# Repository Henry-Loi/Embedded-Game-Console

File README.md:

### This project is inspired by Switch.

## Supported Games
- [X] Tetris
- [X] Asteroid
- [X] Pong
- [X] TicTacToe

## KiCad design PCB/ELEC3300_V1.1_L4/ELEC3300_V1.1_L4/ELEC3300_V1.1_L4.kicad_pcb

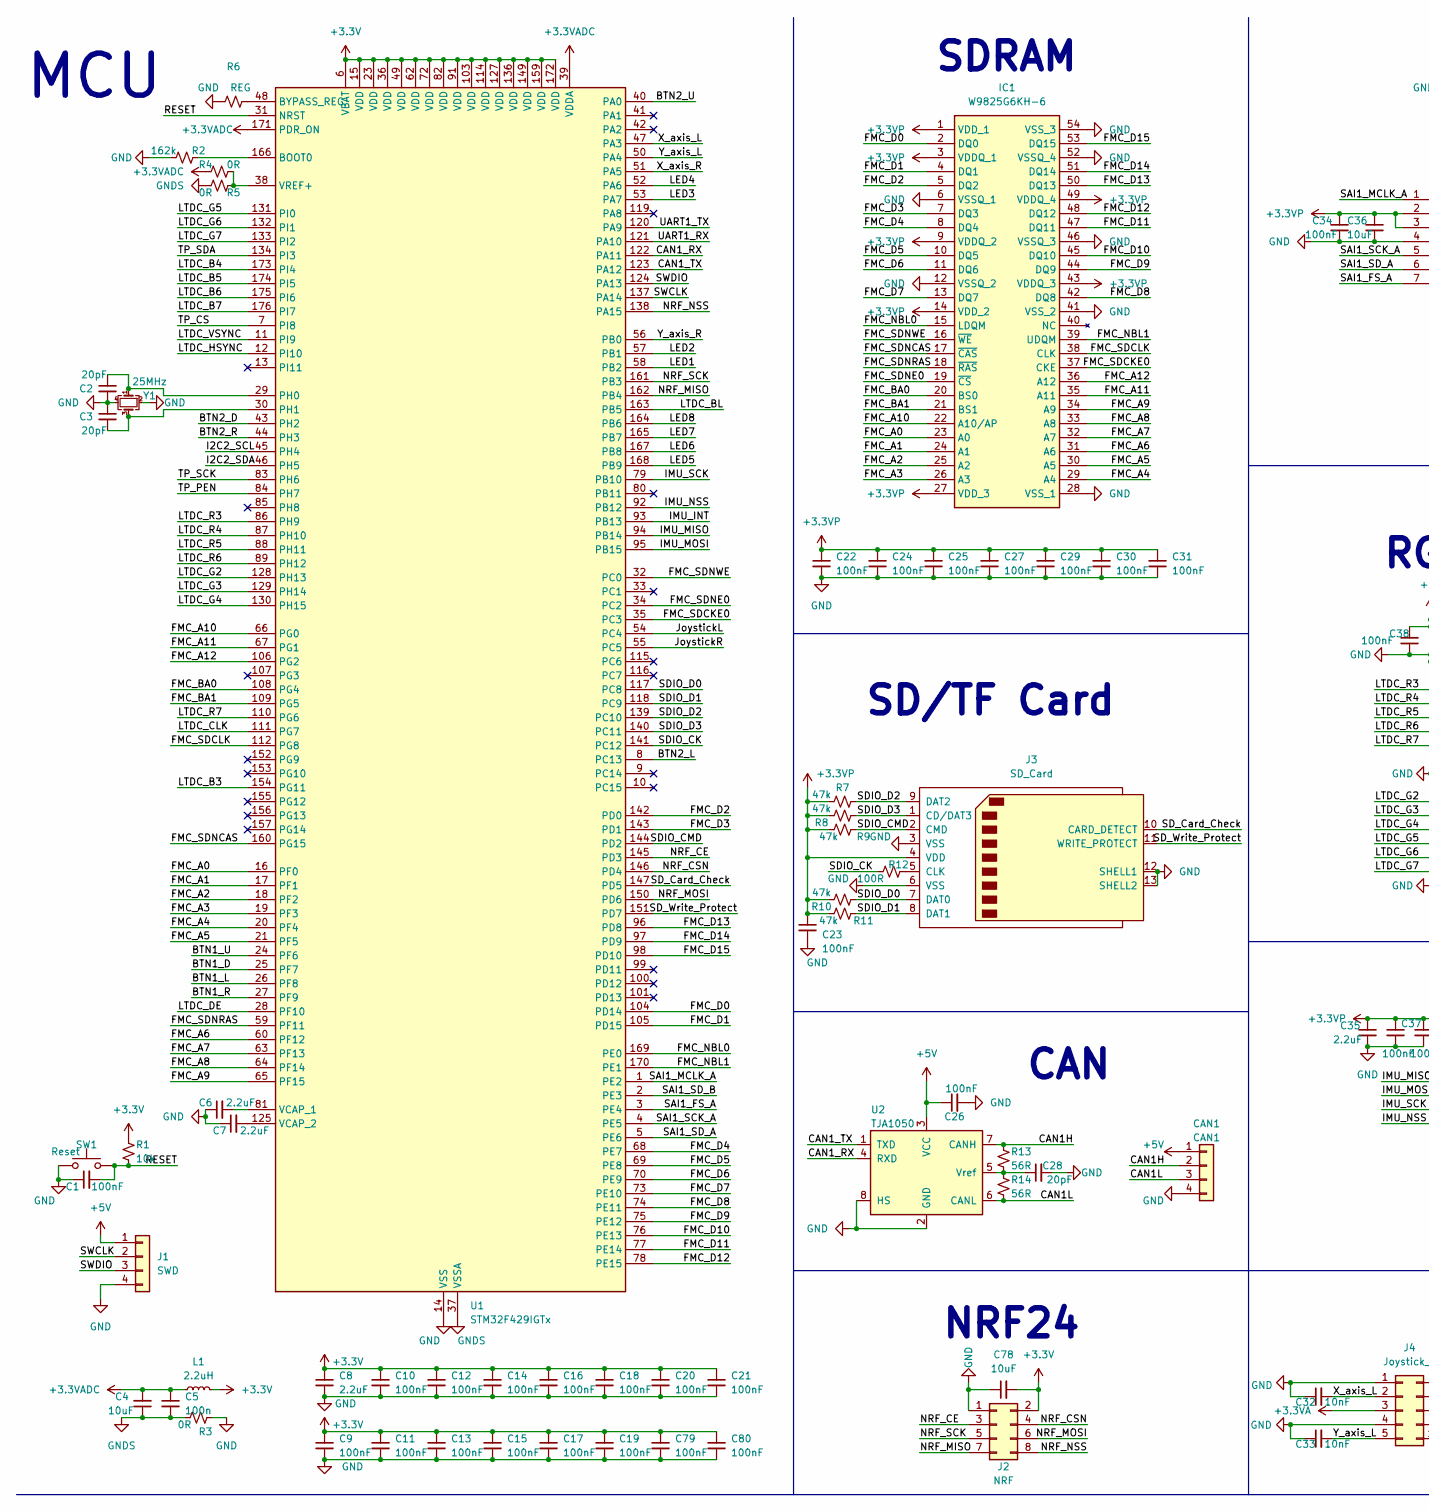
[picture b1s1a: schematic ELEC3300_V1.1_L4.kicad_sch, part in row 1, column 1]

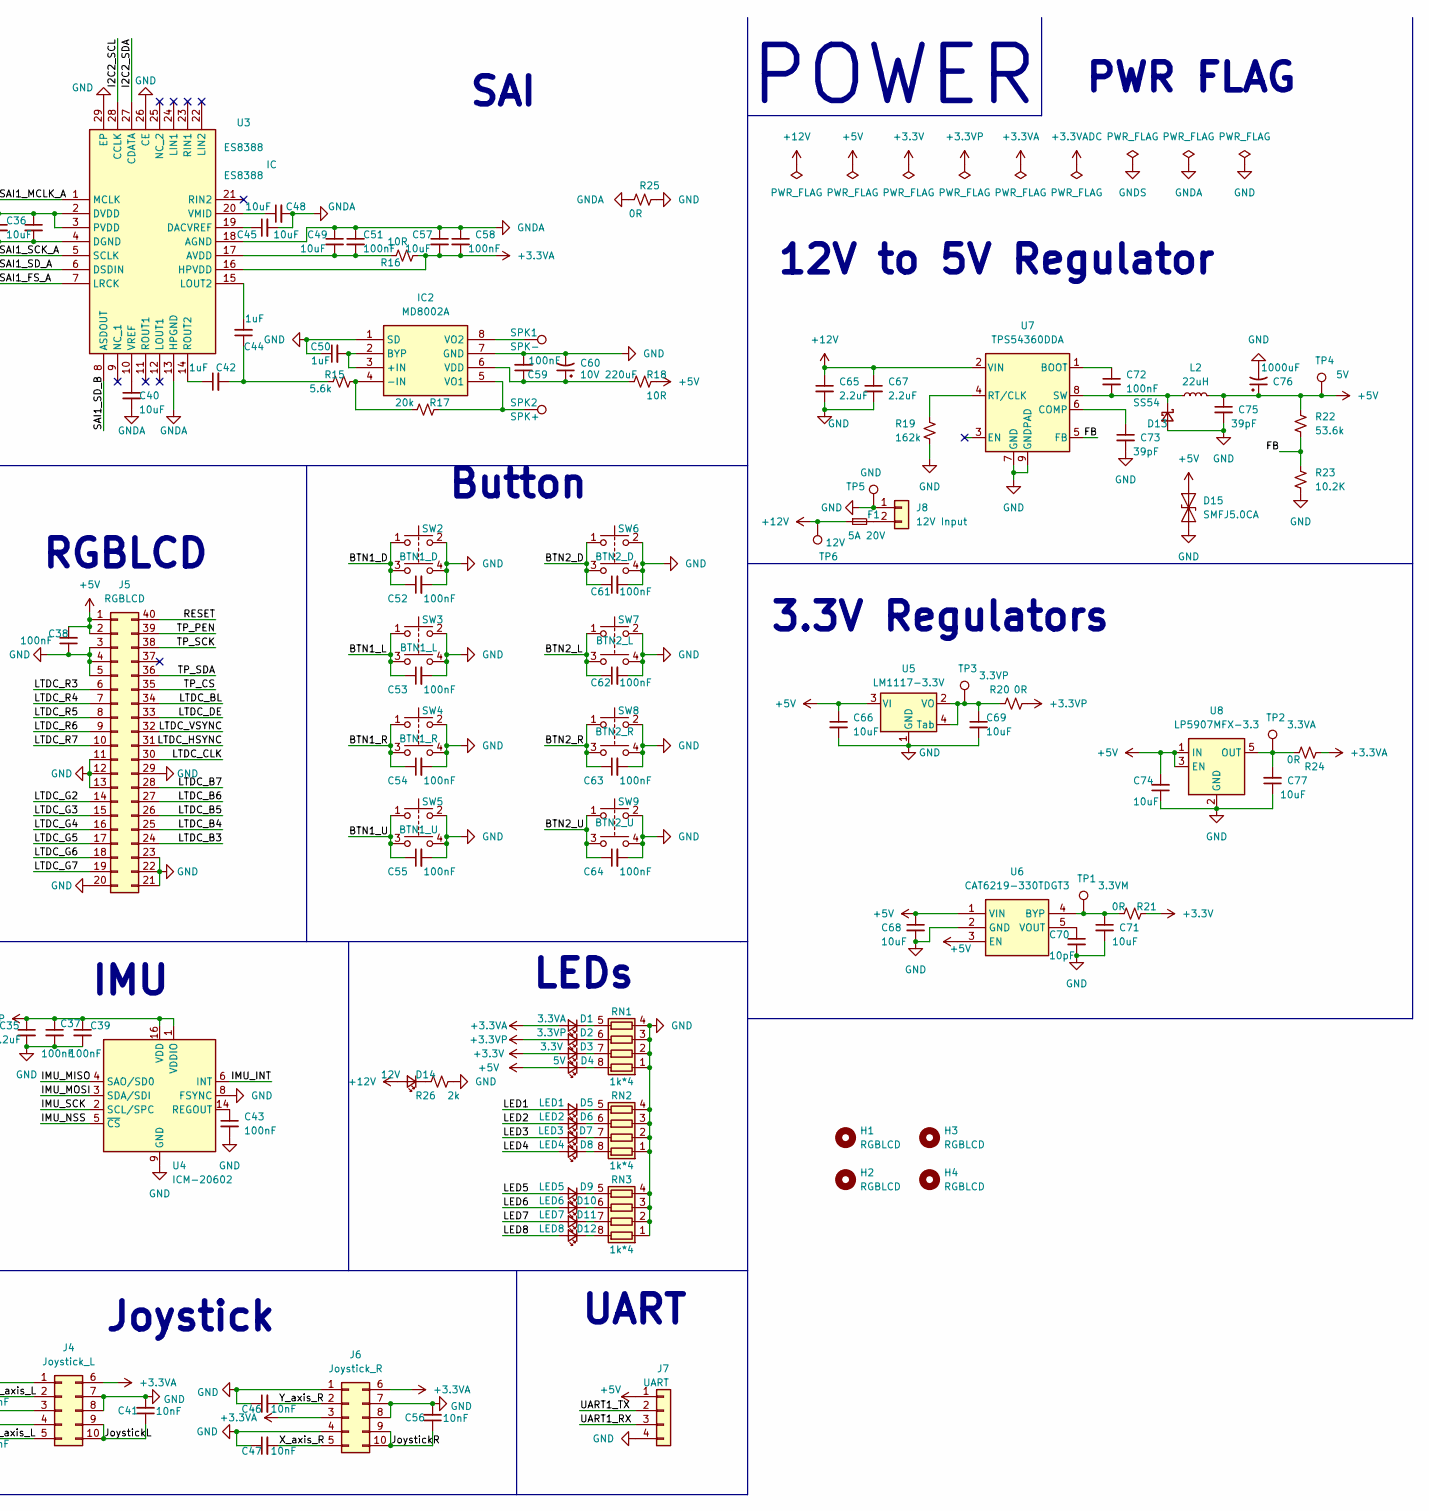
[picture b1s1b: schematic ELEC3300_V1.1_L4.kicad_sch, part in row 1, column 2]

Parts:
C1, C9, C10, C11, C12, C13, C14, C15, C16, C17, C18, C19, C20, C21, C22, C23, C24, C25, C26, C27, C29, C30, C31, C34, C37, C38, C39, C43, C51, C52, C53, C54, C55, C58, C61, C62, C63, C64, C72, C79, C80: 100nF; C_0402_1005Metric_Pad0.74x0.62mm_HandSolder
C2, C3, C28: 20pF; C_0402_1005Metric_Pad0.74x0.62mm_HandSolder
C4, C36, C45, C49, C57: 10uF; C_0402_1005Metric_Pad0.74x0.62mm_HandSolder
C5: 100n; C_0402_1005Metric_Pad0.74x0.62mm_HandSolder
C6, C7, C8, C35: 2.2uF; C_0402_1005Metric_Pad0.74x0.62mm_HandSolder
C32, C33, C41, C46, C47, C56: 10nF; C_0603_1608Metric
C40, C66, C68, C69, C71, C74, C77, C78: 10uF; C_0603_1608Metric
C42, C44, C50: 1uF; C_0603_1608Metric
C48: 10uF; R_0402_1005Metric_Pad0.72x0.64mm_HandSolder
C59: 100nF; C_0603_1608Metric
C60: 10V 220uF; CP_Elec_6.3x5.4
C65, C67: 2.2uF; C_0603_1608Metric
C70: 10pF; C_0603_1608Metric
C73, C75: 39pF; C_0603_1608Metric
C76: 1000uF; CP_Elec_8x10.5
CAN1: CAN1; Molex_SL_171971-0004_1x04_P2.54mm_Vertical
D1: 3.3VA; LED_0603_1608Metric
D2: 3.3VP; LED_0603_1608Metric
D3: 3.3V; LED_0603_1608Metric
D4: 5V; LED_0603_1608Metric
D5: LED1; LED_0603_1608Metric
D6: LED2; LED_0603_1608Metric
D7: LED3; LED_0603_1608Metric
D8: LED4; LED_0603_1608Metric
D9: LED5; LED_0603_1608Metric
D10: LED6; LED_0603_1608Metric
D11: LED7; LED_0603_1608Metric
D12: LED8; LED_0603_1608Metric
D13: SS54; D_SMA
D14: 12V; LED_0603_1608Metric
D15: SMFJ5.0CA; D_SOD-123F
F1: 5A 20V; 1808Fuse_Base
H1, H2, H3, H4: RGBLCD; MountingHole_3.2mm_M3
IC1: W9825G6KH-6; SOP80P1176X120-54N; Manufacturer_Part_Number W9825G6KH-6; Mouser Part Number 454-W9825G6KH-6
IC2: MD8002A; SOIC127P600X175-8N; Manufacturer_Part_Number MD8002A
J1: SWD; Molex_SL_171971-0004_1x04_P2.54mm_Vertical
J2: NRF; PinHeader_2x04_P2.54mm_Vertical
J3: SD_Card; SD_Kyocera_145638009511859+
J4: Joystick_L; XDCR_COM-09032
J5: RGBLCD; Hirose_FH12-40S-0.5SH_1x40-1MP_P0.50mm_Horizontal
J6: Joystick_R; XDCR_COM-09032
J7: UART; Molex_SL_171971-0004_1x04_P2.54mm_Vertical
J8: 12V Input; AMASS_XT30U-M_1x02_P5.0mm_Vertical
L1: 2.2uH; L_0420
L2: 22uH; L_7.3x7.3_H3.5
R1: 10k; R_0402_1005Metric_Pad0.72x0.64mm_HandSolder
R2: 162k; L_0402_1005Metric_Pad0.77x0.64mm_HandSolder
R3, R4, R5, R25: 0R; R_0402_1005Metric_Pad0.72x0.64mm_HandSolder
R6: REG; R_0402_1005Metric_Pad0.72x0.64mm_HandSolder
R7, R8, R9, R10, R11: 47k; R_0402_1005Metric_Pad0.72x0.64mm_HandSolder
R12: 100R; R_0402_1005Metric_Pad0.72x0.64mm_HandSolder
R13, R14: 56R; R_0402_1005Metric_Pad0.72x0.64mm_HandSolder
R15: 5.6k; R_0603_1608Metric
R16, R18: 10R; R_0603_1608Metric
R17: 20k; R_0603_1608Metric
R19: 162k; R_0603_1608Metric
R20, R21, R24: 0R; R_0603_1608Metric_Pad0.98x0.95mm_HandSolder
R22: 53.6k; R_0402_1005Metric_Pad0.72x0.64mm_HandSolder
R23: 10.2K; R_0402_1005Metric_Pad0.72x0.64mm_HandSolder
R26: 2k; R_0603_1608Metric_Pad0.98x0.95mm_HandSolder
RN1, RN2, RN3: 1k*4; R_Array_Concave_4x0402
SPK1: SPK-; TestPoint_Loop_D3.50mm_Drill1.4mm_Beaded
SPK2: SPK+; TestPoint_Loop_D3.50mm_Drill1.4mm_Beaded
SW1: Reset; SW_Push_1P1T_NO_CK_KSC6xxJ
SW2: BTN1_D; SW_B3F-4055
SW3: BTN1_L; SW_B3F-4055
SW4: BTN1_R; SW_B3F-4055
SW5: BTN1_U; SW_B3F-4055
SW6: BTN2_D; SW_B3F-4055
SW7: BTN2_L; SW_B3F-4055
SW8: BTN2_R; SW_B3F-4055
SW9: BTN2_U; SW_B3F-4055
TP1: 3.3VM; TestPoint_Pad_D2.5mm
TP2: 3.3VA; TestPoint_Pad_D2.5mm
TP3: 3.3VP; TestPoint_Pad_D2.5mm
TP4: 5V; TestPoint_Pad_D2.5mm
TP5: GND; TestPoint_Pad_D2.5mm
TP6: 12V; TestPoint_Pad_D2.5mm
U1: STM32F429IGTx; LQFP-176_24x24mm_P0.5mm
U2: TJA1050; SOIC-8_3.9x4.9mm_P1.27mm
U3: ES8388; QFN45P400X400X90-29N-D; Manufacturer_Part_Number ES8388
U4: ICM-20602; LGA-16_3x3mm_P0.5mm_LayoutBorder3x5y
U5: LM1117-3.3V; SOT-223
U6: CAT6219-330TDGT3; SOT95P280X100-5N; Manufacturer_Part_Number CAT6219-330TDGT3; Mouser Part Number 698-CAT6219-330TD-G
U7: TPS54360DDA; TI_SO-PowerPAD-8_ThermalVias
U8: LP5907MFX-3.3; SOT-23-5
Y1: 25MHz; Crystal_SMD_3225-4Pin_3.2x2.5mm

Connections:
+3.3V: C8.1, C9.1, C10.1, C11.1, C12.1, C13.1, C14.1, C15.1, C16.1, C17.1, C18.1, C19.1, C20.1, C21.1, C78.2, C79.1, C80.1, D3.2 (A), J2.2, L1.2, R1.2, R21.2, U1.6 (VBAT), U1.15 (VDD), U1.23 (VDD), U1.36 (VDD), U1.49 (VDD), U1.62 (VDD), U1.72 (VDD), U1.82 (VDD), U1.91 (VDD), U1.103 (VDD), U1.114 (VDD), U1.127 (VDD), U1.136 (VDD), U1.149 (VDD), U1.159 (VDD), U1.172 (VDD)
+3.3VA: C57.2, C58.2, D1.2 (A), J4.3, J4.6, J6.3, J6.6, R16.2, R24.2, U3.16 (HPVDD)
+3.3VADC: C4.2, C5.1, L1.1, R4.1, U1.39 (VDDA), U1.171 (PDR_ON)
+3.3VP: C22.1, C23.1, C24.1, C25.1, C27.1, C29.1, C30.1, C31.1, C34.1, C35.1, C36.1, C37.1, C39.1, D2.2 (A), IC1.1 (VDD_1), IC1.3 (VDDQ_1), IC1.9 (VDDQ_2), IC1.14 (VDD_2), IC1.27 (VDD_3), IC1.43 (VDDQ_3), IC1.49 (VDDQ_4), J3.4 (VDD), R7.1, R8.1, R9.1, R10.1, R11.1, R20.2, U3.2 (DVDD), U3.3 (PVDD), U4.1 (VDDIO), U4.16 (VDD)
+5V: C26.1, C38.2, C66.1, C68.1, C74.2, C75.1, C76.1, CAN1.1, D4.2 (A), D15.1 (A1), J1.1, J5.1, J5.2, J7.1, L2.2, R18.2, R22.1, TP4.1, U2.3 (VCC), U5.3 (VI), U6.1 (VIN), U6.3 (EN), U8.1 (IN), U8.3 (EN)
+12V: C65.1, C67.1, D14.2 (A), F1.1, TP6.1, U7.2 (VIN)
/BTN1_D: C52.1, SW2.1, SW2.3, U1.25 (PF7)
/BTN1_L: C53.1, SW3.1, SW3.3, U1.26 (PF8)
/BTN1_R: C54.1, SW4.1, SW4.3, U1.27 (PF9)
/BTN1_U: C55.1, SW5.1, SW5.3, U1.24 (PF6)
/BTN2_D: C61.1, SW6.1, SW6.3, U1.43 (PH2)
/BTN2_L: C62.1, SW7.1, SW7.3, U1.8 (PC13)
/BTN2_R: C63.1, SW8.1, SW8.3, U1.44 (PH3)
/BTN2_U: C64.1, SW9.1, SW9.3, U1.40 (PA0)
/CAN1H: CAN1.2, R13.1, U2.7 (CANH)
/CAN1L: CAN1.3, R14.2, U2.6 (CANL)
/CAN1_RX: U1.122 (PA11), U2.4 (RXD)
/CAN1_TX: U1.123 (PA12), U2.1 (TXD)
/FB: R22.2, R23.1, U7.5 (FB)
/FMC_A0: IC1.23 (A0), U1.16 (PF0)
/FMC_A1: IC1.24 (A1), U1.17 (PF1)
/FMC_A2: IC1.25 (A2), U1.18 (PF2)
/FMC_A3: IC1.26 (A3), U1.19 (PF3)
/FMC_A4: IC1.29 (A4), U1.20 (PF4)
/FMC_A5: IC1.30 (A5), U1.21 (PF5)
/FMC_A6: IC1.31 (A6), U1.60 (PF12)
/FMC_A7: IC1.32 (A7), U1.63 (PF13)
/FMC_A8: IC1.33 (A8), U1.64 (PF14)
/FMC_A9: IC1.34 (A9), U1.65 (PF15)
/FMC_A10: IC1.22 (A10/AP), U1.66 (PG0)
/FMC_A11: IC1.35 (A11), U1.67 (PG1)
/FMC_A12: IC1.36 (A12), U1.106 (PG2)
/FMC_BA0: IC1.20 (BS0), U1.108 (PG4)
/FMC_BA1: IC1.21 (BS1), U1.109 (PG5)
/FMC_D0: IC1.2 (DQ0), U1.104 (PD14)
/FMC_D1: IC1.4 (DQ1), U1.105 (PD15)
/FMC_D2: IC1.5 (DQ2), U1.142 (PD0)
/FMC_D3: IC1.7 (DQ3), U1.143 (PD1)
/FMC_D4: IC1.8 (DQ4), U1.68 (PE7)
/FMC_D5: IC1.10 (DQ5), U1.69 (PE8)
/FMC_D6: IC1.11 (DQ6), U1.70 (PE9)
/FMC_D7: IC1.13 (DQ7), U1.73 (PE10)
/FMC_D8: IC1.42 (DQ8), U1.74 (PE11)
/FMC_D9: IC1.44 (DQ9), U1.75 (PE12)
/FMC_D10: IC1.45 (DQ10), U1.76 (PE13)
/FMC_D11: IC1.47 (DQ11), U1.77 (PE14)
/FMC_D12: IC1.48 (DQ12), U1.78 (PE15)
/FMC_D13: IC1.50 (DQ13), U1.96 (PD8)
/FMC_D14: IC1.51 (DQ14), U1.97 (PD9)
/FMC_D15: IC1.53 (DQ15), U1.98 (PD10)
/FMC_NBL0: IC1.15 (LDQM), U1.169 (PE0)
/FMC_NBL1: IC1.39 (UDQM), U1.170 (PE1)
/FMC_SDCKE0: IC1.37 (CKE), U1.35 (PC3)
/FMC_SDCLK: IC1.38 (CLK), U1.112 (PG8)
/FMC_SDNCAS: IC1.17 (~CAS), U1.160 (PG15)
/FMC_SDNE0: IC1.19 (~CS), U1.34 (PC2)
/FMC_SDNRAS: IC1.18 (~RAS), U1.59 (PF11)
/FMC_SDNWE: IC1.16 (~WE), U1.32 (PC0)
/I2C2_SCL: U1.45 (PH4), U3.28 (CCLK)
/I2C2_SDA: U1.46 (PH5), U3.27 (CDATA)
/IMU_INT: U1.93 (PB13), U4.6 (INT)
/IMU_MISO: U1.94 (PB14), U4.4 (SAO/SD0)
/IMU_MOSI: U1.95 (PB15), U4.3 (SDA/SDI)
/IMU_NSS: U1.92 (PB12), U4.5 (~CS)
/IMU_SCK: U1.79 (PB10), U4.2 (SCL/SPC)
/JoystickL: C41.1, J4.9, J4.10, U1.54 (PC4)
/JoystickR: C56.1, J6.9, J6.10, U1.55 (PC5)
/LED1: D5.2 (A), U1.58 (PB2)
/LED2: D6.2 (A), U1.57 (PB1)
/LED3: D7.2 (A), U1.53 (PA7)
/LED4: D8.2 (A), U1.52 (PA6)
/LED5: D9.2 (A), U1.168 (PB9)
/LED6: D10.2 (A), U1.167 (PB8)
/LED7: D11.2 (A), U1.165 (PB7)
/LED8: D12.2 (A), U1.164 (PB6)
/LTDC_B3: J5.24, U1.154 (PG11)
/LTDC_B4: J5.25, U1.173 (PI4)
/LTDC_B5: J5.26, U1.174 (PI5)
/LTDC_B6: J5.27, U1.175 (PI6)
/LTDC_B7: J5.28, U1.176 (PI7)
/LTDC_BL: J5.34, U1.163 (PB5)
/LTDC_CLK: J5.30, U1.111 (PG7)
/LTDC_DE: J5.33, U1.28 (PF10)
/LTDC_G2: J5.14, U1.128 (PH13)
/LTDC_G3: J5.15, U1.129 (PH14)
/LTDC_G4: J5.16, U1.130 (PH15)
/LTDC_G5: J5.17, U1.131 (PI0)
/LTDC_G6: J5.18, U1.132 (PI1)
/LTDC_G7: J5.19, U1.133 (PI2)
/LTDC_HSYNC: J5.31, U1.12 (PI10)
/LTDC_R3: J5.6, U1.86 (PH9)
/LTDC_R4: J5.7, U1.87 (PH10)
/LTDC_R5: J5.8, U1.88 (PH11)
/LTDC_R6: J5.9, U1.89 (PH12)
/LTDC_R7: J5.10, U1.110 (PG6)
/LTDC_VSYNC: J5.32, U1.11 (PI9)
/NRF_CE: J2.3, U1.145 (PD3)
/NRF_CSN: J2.4, U1.146 (PD4)
/NRF_MISO: J2.7, U1.162 (PB4)
/NRF_MOSI: J2.6, U1.150 (PD6)
/NRF_NSS: J2.8, U1.138 (PA15)
/NRF_SCK: J2.5, U1.161 (PB3)
/RESET: C1.2, J5.40, R1.1, SW1.2, U1.31 (NRST)
/SAI1_FS_A: U1.3 (PE4), U3.7 (LRCK)
/SAI1_MCLK_A: U1.1 (PE2), U3.1 (MCLK)
/SAI1_SCK_A: U1.4 (PE5), U3.5 (SCLK)
/SAI1_SD_A: U1.5 (PE6), U3.6 (DSDIN)
/SAI1_SD_B: U1.2 (PE3), U3.8 (ASDOUT)
/SDIO_CK: R12.1, U1.141 (PC12)
/SDIO_CMD: J3.2 (CMD), R9.2, U1.144 (PD2)
/SDIO_D0: J3.7 (DAT0), R10.2, U1.117 (PC8)
/SDIO_D1: J3.8 (DAT1), R11.2, U1.118 (PC9)
/SDIO_D2: J3.9 (DAT2), R7.2, U1.139 (PC10)
/SDIO_D3: J3.1 (CD/DAT3), R8.2, U1.140 (PC11)
/SD_Card_Check: J3.10 (CARD_DETECT), U1.147 (PD5)
/SD_Write_Protect: J3.11 (WRITE_PROTECT), U1.151 (PD7)
/SWCLK: J1.2, U1.137 (PA14)
/SWDIO: J1.3, U1.124 (PA13)
/TP_CS: J5.35, U1.7 (PI8)
/TP_PEN: J5.39, U1.84 (PH7)
/TP_SCK: J5.38, U1.83 (PH6)
/TP_SDA: J5.36, U1.134 (PI3)
/UART1_RX: J7.3, U1.121 (PA10)
/UART1_TX: J7.2, U1.120 (PA9)
/X_axis_L: C32.2, J4.2, U1.47 (PA3)
/X_axis_R: C47.2, J6.5, U1.51 (PA5)
/Y_axis_L: C33.2, J4.5, U1.50 (PA4)
/Y_axis_R: C46.2, J6.2, U1.56 (PB0)
GND: C1.1, C2.2, C3.1, C6.1, C7.1, C8.2, C9.2, C10.2, C11.2, C12.2, C13.2, C14.2, C15.2, C16.2, C17.2, C18.2, C19.2, C20.2, C21.2, C22.2, C23.2, C24.2, C25.2, C26.2, C27.2, C28.2, C29.2, C30.2, C31.2, C32.1, C33.1, C34.2, C35.2, C36.2, C37.2, C38.1, C39.2, C41.2, C43.2, C46.1, C47.1, C50.1, C52.2, C53.2, C54.2, C55.2, C56.2, C59.2, C60.2, C61.2, C62.2, C63.2, C64.2, C65.2, C66.2, C67.2, C68.2, C69.2, C70.2, C71.2, C73.2, C74.1, C75.2, C76.2, C77.1, C78.1, C79.2, C80.2, CAN1.4, D13.2 (A), D15.2 (A2), IC1.6 (VSSQ_1), IC1.12 (VSSQ_2), IC1.28 (VSS_1), IC1.41 (VSS_2), IC1.46 (VSSQ_3), IC1.52 (VSSQ_4), IC1.54 (VSS_3), IC2.1 (SD), IC2.7 (GND)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
GNDA: C40.2, C45.2, C48.2, C49.1, C51.1, C57.1, C58.1, R25.1, U3.13 (HPGND), U3.18 (AGND)
GNDS: C4.1, C5.2, R3.1, R5.1, U1.37 (VSSA)
unnamed: C42.2, C44.1, R15.1
unnamed: D1.1 (K), RN1.5 (R4.2)
unnamed: D2.1 (K), RN1.6 (R3.2)
unnamed: D3.1 (K), RN1.7 (R2.2)
unnamed: D4.1 (K), RN1.8 (R1.2)
unnamed: D5.1 (K), RN2.5 (R4.2)
unnamed: D6.1 (K), RN2.6 (R3.2)
unnamed: D7.1 (K), RN2.7 (R2.2)
unnamed: D8.1 (K), RN2.8 (R1.2)
unnamed: D9.1 (K), RN3.5 (R4.2)
unnamed: D10.1 (K), RN3.6 (R3.2)
unnamed: D11.1 (K), RN3.7 (R2.2)
unnamed: D12.1 (K), RN3.8 (R1.2)
unnamed: C72.2, D13.1 (K), L2.1, U7.8 (SW)
unnamed: D14.1 (K), R26.1
unnamed: C50.2, IC2.2 (BYP), IC2.3 (+IN)
unnamed: IC2.4 (-IN), R15.2, R17.1
unnamed: C59.1, C60.1, IC2.6 (VDD), R18.1
unnamed: IC2.5 (VO1), R17.2, SPK2.1
unnamed: IC2.8 (VO2), SPK1.1
unnamed: J3.5 (CLK), R12.2
unnamed: F1.2, J8.2
unnamed: R2.2, U1.166 (BOOT0)
unnamed: R6.2, U1.48 (BYPASS_REG)
unnamed: C2.1, U1.29 (PH0), Y1.1
unnamed: C3.2, U1.30 (PH1), Y1.3
unnamed: C6.2, U1.81 (VCAP_1)
unnamed: C7.2, U1.125 (VCAP_2)
unnamed: R4.2, R5.2, U1.38 (VREF+)
unnamed: C28.1, R13.2, R14.1, U2.5 (Vref)
unnamed: C49.2, C51.2, R16.1, U3.17 (AVDD)
unnamed: C45.1, U3.19 (DACVREF)
unnamed: C44.2, U3.15 (LOUT2)
unnamed: C42.1, U3.14 (ROUT2)
unnamed: C48.1, U3.20 (VMID)
unnamed: C40.1, U3.10 (VREF)
unnamed: C43.1, U4.14 (REGOUT)
unnamed: C69.1, R20.1, TP3.1, U5.2 (VO), U5.4 (Tab)
unnamed: C71.1, R21.1, TP1.1, U6.4 (BYP)
unnamed: C70.1, U6.5 (VOUT)
unnamed: C72.1, U7.1 (BOOT)
unnamed: C73.1, U7.6 (COMP)
unnamed: R19.1, U7.4 (RT/CLK)
unnamed: C77.2, R24.1, TP2.1, U8.5 (OUT)

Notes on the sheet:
3.3V Regulators
MCU
POWER
IMU
LEDs
Joystick
SAI
UART
PWR FLAG
12V to 5V Regulator
CAN
Button
RGBLCD
SD/TF Card
NRF24
SDRAM

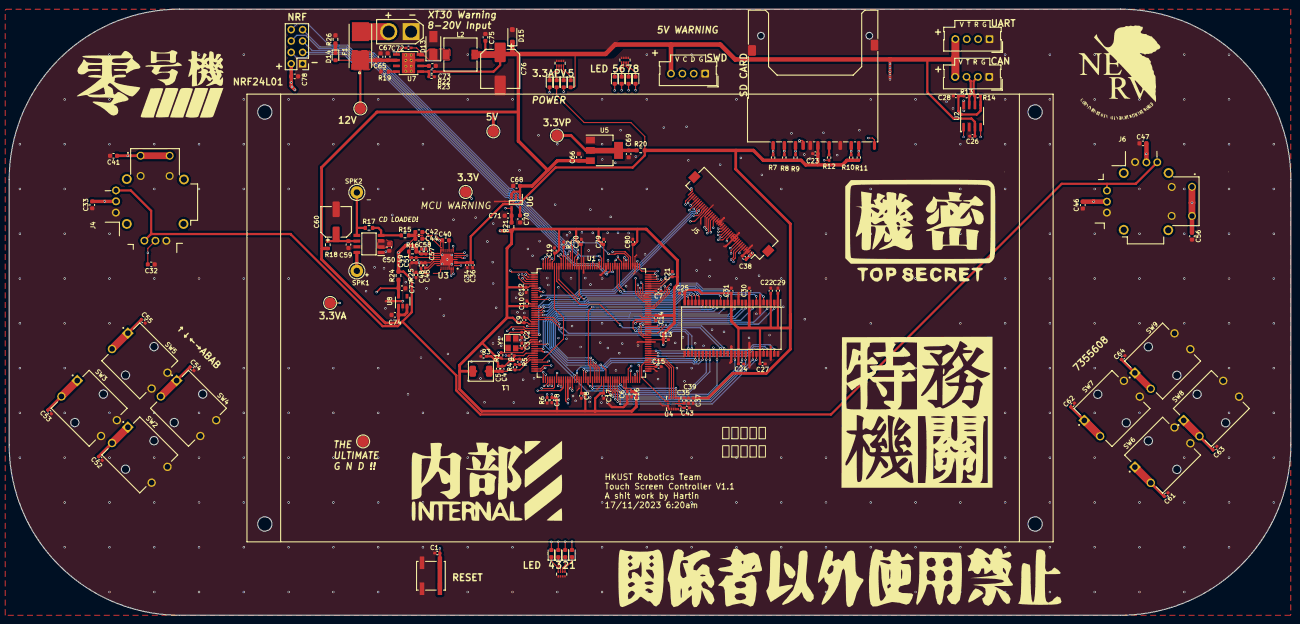
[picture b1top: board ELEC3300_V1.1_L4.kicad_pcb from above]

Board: 4 copper layers, 286.2 x 135.3 mm, 168 parts (0 on the bottom side), 175 nets.

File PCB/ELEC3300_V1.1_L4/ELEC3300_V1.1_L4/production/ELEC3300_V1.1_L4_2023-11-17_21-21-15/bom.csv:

Designator,Footprint,Quantity,Value,LCSC Part #
"C1, C10, C11, C12, C13, C14, C15, C16, C17, C18, C19, C20, C21, C22, C23, C24, C25, C26, C27, C29, C30, C31, C34, C37, C38, C39, C43, C51, C52, C53, C54, C55, C58, C61, C62, C63, C64, C72, C79, C80, C9",0402,41,100nF,
"C2, C28, C3",0402,3,20pF,
"C32, C33, C41, C46, C47, C56",0603,6,10nF,
"C35, C6, C7, C8",0402,4,2.2uF,
"C36, C4, C45, C48, C49, C57",0402,6,10uF,
"C40, C66, C68, C69, C71, C74, C77, C78",0603,8,10uF,
"C42, C44, C50",0603,3,1uF,
C5,0402,1,100n,
C59,0603,1,100nF,
C60,CP_Elec_6.3x5.4,1,10V 220uF,
"C65, C67",0603,2,2.2uF,
C70,0603,1,10pF,
"C73, C75",0603,2,39pF,
C76,CP_Elec_8x10.5,1,1000uF,
CAN1,Molex_SL_171971-0004_1x04_P2.54mm_Vertical,1,CAN1,
D1,0603,1,3.3VA,
D10,0603,1,LED6,
D11,0603,1,LED7,
D12,0603,1,LED8,
D13,D_SMA,1,SS54,
D14,0603,1,12V,
D15,D_SOD-123F,1,SMFJ5.0CA,
D2,0603,1,3.3VP,
D3,0603,1,3.3V,
D4,0603,1,5V,
D5,0603,1,LED1,
D6,0603,1,LED2,
D7,0603,1,LED3,
D8,0603,1,LED4,
D9,0603,1,LED5,
F1,1808Fuse_Base,1,5A 20V,
"H1, H2, H3, H4",MountingHole_3.2mm_M3,4,RGBLCD,
IC1,SOP80P1176X120-54N,1,W9825G6KH-6,
IC2,SOIC127P600X175-8N,1,MD8002A,
J1,Molex_SL_171971-0004_1x04_P2.54mm_Vertical,1,SWD,
J2,PinHeader_2x04_P2.54mm_Vertical,1,NRF,
J3,SD_Kyocera_145638009511859+,1,SD_Card,
J4,XDCR_COM-09032,1,Joystick_L,
J5,Hirose_FH12-40S-0.5SH_1x40-1MP_P0.50mm_Horizontal,1,RGBLCD,
J6,XDCR_COM-09032,1,Joystick_R,
J7,Molex_SL_171971-0004_1x04_P2.54mm_Vertical,1,UART,
J8,AMASS_XT30U-M_1x02_P5.0mm_Vertical,1,12V Input,
L1,L_0420,1,2.2uH,
L2,L_7.3x7.3_H3.5,1,22uH,
R1,0402,1,10k,
"R10, R11, R7, R8, R9",0402,5,47k,
R12,0402,1,100R,
"R13, R14",0402,2,56R,
R15,0603,1,5.6k,
"R16, R18",0603,2,10R,
R17,0603,1,20k,
R19,0603,1,162k,
R2,0402,1,162k,
"R20, R21, R24",0603,3,0R,
R22,0402,1,53.6k,
R23,0402,1,10.2K,
"R25, R3, R4, R5",0402,4,0R,
R26,0603,1,2k,
R6,0402,1,REG,
"RN1, RN2, RN3",R_Array_Concave_4x0402,3,1k*4,
SPK1,TestPoint_Loop_D3.50mm_Drill1.4mm_Beaded,1,SPK-,
SPK2,TestPoint_Loop_D3.50mm_Drill1.4mm_Beaded,1,SPK+,
SW1,SW_Push_1P1T_NO_CK_KSC6xxJ,1,Reset,
SW2,SW_B3F-4055,1,BTN1_D,
SW3,SW_B3F-4055,1,BTN1_L,
SW4,SW_B3F-4055,1,BTN1_R,
SW5,SW_B3F-4055,1,BTN1_U,
SW6,SW_B3F-4055,1,BTN2_D,
SW7,SW_B3F-4055,1,BTN2_L,
SW8,SW_B3F-4055,1,BTN2_R,
SW9,SW_B3F-4055,1,BTN2_U,
TP1,TestPoint_Pad_D2.5mm,1,3.3VM,
TP2,TestPoint_Pad_D2.5mm,1,3.3VA,
TP3,TestPoint_Pad_D2.5mm,1,3.3VP,
TP4,TestPoint_Pad_D2.5mm,1,5V,
TP5,TestPoint_Pad_D2.5mm,1,GND,
TP6,TestPoint_Pad_D2.5mm,1,12V,
U1,LQFP-176_24x24mm_P0.5mm,1,STM32F429IGTx,
U2,SOIC-8_3.9x4.9mm_P1.27mm,1,TJA1050,
U3,QFN45P400X400X90-29N-D,1,ES8388,
U4,LGA-16_3x3mm_P0.5mm_LayoutBorder3x5y,1,ICM-20602,
U5,SOT-223,1,LM1117-3.3V,
U6,SOT95P280X100-5N,1,CAT6219-330TDGT3,
U7,TI_SO-PowerPAD-8_ThermalVias,1,TPS54360DDA,
U8,SOT-23-5,1,LP5907MFX-3.3,
Y1,Crystal_SMD_3225-4Pin_3.2x2.5mm,1,25MHz,

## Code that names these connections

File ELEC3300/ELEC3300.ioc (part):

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Mcu.Name=STM32F429I(E-G)Tx
Mcu.Package=LQFP176
Mcu.UserName=STM32F429IGTx
PA0/WKUP.GPIOParameters=GPIO_PuPd,GPIO_Label
PA0/WKUP.GPIO_Label=RBTN_UP
PA0/WKUP.GPIO_PuPd=GPIO_PULLUP
PA0/WKUP.Signal=GPIO_Input
PA10.Mode=Asynchronous
PA10.Signal=USART1_RX
PA13.Mode=Serial_Wire
PA13.Signal=SYS_JTMS-SWDIO
PA14.Mode=Serial_Wire
PA14.Signal=SYS_JTCK-SWCLK
PA3.Signal=ADCx_IN3
PA4.Signal=ADCx_IN4
PA5.Signal=ADCx_IN5
PA6.GPIOParameters=GPIO_Label
PA6.GPIO_Label=LED4
PA6.Signal=GPIO_Output
PA7.GPIOParameters=GPIO_Label
PA7.GPIO_Label=LED3
PA7.Signal=GPIO_Output
PA9.Mode=Asynchronous
PA9.Signal=USART1_TX
PB0.Signal=ADCx_IN8
PB1.GPIOParameters=GPIO_Label
PB1.GPIO_Label=LED2
PB1.Signal=GPIO_Output
PB10.Mode=Full_Duplex_Master
PB10.Signal=SPI2_SCK
PB12.GPIOParameters=GPIO_PuPd,GPIO_Label
PB12.GPIO_Label=IMU_CS
PB12.GPIO_PuPd=GPIO_PULLUP
PB12.Signal=GPIO_Output
PB13.GPIOParameters=GPIO_Label
PB13.GPIO_Label=IMU_INT
PB13.Signal=GPIO_Input
PB14.Mode=Full_Duplex_Master
PB14.Signal=SPI2_MISO
PB15.Mode=Full_Duplex_Master
PB15.Signal=SPI2_MOSI
PB2/BOOT1.GPIOParameters=GPIO_Label
PB2/BOOT1.GPIO_Label=LED1
PB2/BOOT1.Signal=GPIO_Output
PB5.Signal=S_TIM3_CH2
PB6.GPIOParameters=GPIO_Label
PB6.GPIO_Label=LED8
PB6.Signal=GPIO_Output
PB7.GPIOParameters=GPIO_Label
PB7.GPIO_Label=LED7
PB7.Signal=GPIO_Output
PB8.GPIOParameters=GPIO_Label
PB8.GPIO_Label=LED6
PB8.Signal=GPIO_Output
PB9.GPIOParameters=GPIO_Label
PB9.GPIO_Label=LED5
PB9.Signal=GPIO_Output
PC0.Signal=FMC_SDNWE
PC10.Mode=SD_4_bits_Wide_bus
PC10.Signal=SDIO_D2
PC11.Mode=SD_4_bits_Wide_bus
PC11.Signal=SDIO_D3
PC12.Mode=SD_4_bits_Wide_bus
PC12.Signal=SDIO_CK
PC13.GPIOParameters=GPIO_PuPd,GPIO_Label
PC13.GPIO_Label=RBTN_LEFT
PC13.GPIO_PuPd=GPIO_PULLUP
PC13.Signal=GPIO_Input
PC14/OSC32_IN.Mode=LSE-External-Oscillator
PC14/OSC32_IN.Signal=RCC_OSC32_IN
PC15/OSC32_OUT.Mode=LSE-External-Oscillator
PC15/OSC32_OUT.Signal=RCC_OSC32_OUT
PC2.Mode=SdramChipSelect1_1
PC2.Signal=FMC_SDNE0
PC3.Mode=SdramChipSelect1_1
PC3.Signal=FMC_SDCKE0
PC4.GPIOParameters=GPIO_PuPd,GPIO_Label
PC4.GPIO_Label=Joy_L_Btn
PC4.GPIO_PuPd=GPIO_PULLUP
PC4.Signal=GPIO_Input
PC5.GPIOParameters=GPIO_PuPd,GPIO_Label
PC5.GPIO_Label=Joy_R_Btn
PC5.GPIO_PuPd=GPIO_PULLUP
PC5.Signal=GPIO_Input
PC8.Mode=SD_4_bits_Wide_bus
PC8.Signal=SDIO_D0
PC9.Mode=SD_4_bits_Wide_bus
PC9.Signal=SDIO_D1
PD0.Signal=FMC_D2_DA2
PD1.Signal=FMC_D3_DA3
PD10.Signal=FMC_D15_DA15
PD14.Signal=FMC_D0_DA0
PD15.Signal=FMC_D1_DA1
PD2.Mode=SD_4_bits_Wide_bus
PD2.Signal=SDIO_CMD
PD5.GPIOParameters=GPIO_PuPd,GPIO_Label
PD5.GPIO_Label=SD_Card_Check
PD5.GPIO_PuPd=GPIO_NOPULL
PD5.Signal=GPIO_Input
PD8.Signal=FMC_D13_DA13
PD9.Signal=FMC_D14_DA14
PE0.Signal=FMC_NBL0
PE1.Signal=FMC_NBL1
PE10.Signal=FMC_D7_DA7
PE11.Signal=FMC_D8_DA8
PE12.Signal=FMC_D9_DA9
PE13.Signal=FMC_D10_DA10
PE14.Signal=FMC_D11_DA11
PE15.Signal=FMC_D12_DA12
PE7.Signal=FMC_D4_DA4
PE8.Signal=FMC_D5_DA5
PE9.Signal=FMC_D6_DA6
PF0.Signal=FMC_A0
PF1.Signal=FMC_A1
PF10.GPIOParameters=GPIO_Speed
PF10.GPIO_Speed=GPIO_SPEED_FREQ_VERY_HIGH
PF10.Mode=RGB565
PF10.Signal=LTDC_DE
PF11.Signal=FMC_SDNRAS
PF12.Signal=FMC_A6
PF13.Signal=FMC_A7
PF14.Signal=FMC_A8
PF15.Signal=FMC_A9
PF2.Signal=FMC_A2
PF3.Signal=FMC_A3
PF4.Signal=FMC_A4
PF5.Signal=FMC_A5
PF6.GPIOParameters=GPIO_PuPd,GPIO_Label
PF6.GPIO_Label=LBTN_UP
PF6.GPIO_PuPd=GPIO_PULLUP
PF6.Signal=GPIO_Input
PF7.GPIOParameters=GPIO_PuPd,GPIO_Label
PF7.GPIO_Label=LBTN_DOWN
PF7.GPIO_PuPd=GPIO_PULLUP
PF7.Signal=GPIO_Input
PF8.GPIOParameters=GPIO_PuPd,GPIO_Label
PF8.GPIO_Label=LBTN_LEFT
PF8.GPIO_PuPd=GPIO_PULLUP
PF8.Signal=GPIO_Input
PF9.GPIOParameters=GPIO_PuPd,GPIO_Label
PF9.GPIO_Label=LBTN_RIGHT
PF9.GPIO_PuPd=GPIO_PULLUP
PF9.Signal=GPIO_Input
PG0.Signal=FMC_A10
PG1.Signal=FMC_A11
PG11.GPIOParameters=GPIO_Speed
PG11.GPIO_Speed=GPIO_SPEED_FREQ_VERY_HIGH
PG11.Mode=RGB565
PG11.Signal=LTDC_B3
PG15.Signal=FMC_SDNCAS
PG2.Signal=FMC_A12
PG4.Signal=FMC_A14_BA0
PG5.Signal=FMC_A15_BA1
PG6.GPIOParameters=GPIO_Speed
PG6.GPIO_Speed=GPIO_SPEED_FREQ_VERY_HIGH
PG6.Mode=RGB565
PG6.Signal=LTDC_R7
PG7.GPIOParameters=GPIO_Speed
PG7.GPIO_Speed=GPIO_SPEED_FREQ_VERY_HIGH
PG7.Mode=RGB565
PG7.Signal=LTDC_CLK
PG8.Signal=FMC_SDCLK
PH0/OSC_IN.Mode=HSE-External-Oscillator
PH0/OSC_IN.Signal=RCC_OSC_IN
PH1/OSC_OUT.Mode=HSE-External-Oscillator
PH1/OSC_OUT.Signal=RCC_OSC_OUT
PH10.GPIOParameters=GPIO_Speed
PH10.GPIO_Speed=GPIO_SPEED_FREQ_VERY_HIGH
PH10.Mode=RGB565
PH10.Signal=LTDC_R4
PH11.GPIOParameters=GPIO_Speed
PH11.GPIO_Speed=GPIO_SPEED_FREQ_VERY_HIGH
PH11.Mode=RGB565
PH11.Signal=LTDC_R5
PH12.GPIOParameters=GPIO_Speed
PH12.GPIO_Speed=GPIO_SPEED_FREQ_VERY_HIGH
PH12.Mode=RGB565
PH12.Signal=LTDC_R6
PH13.GPIOParameters=GPIO_Speed
PH13.GPIO_Speed=GPIO_SPEED_FREQ_VERY_HIGH
PH13.Mode=RGB565
PH13.Signal=LTDC_G2
PH14.GPIOParameters=GPIO_Speed
PH14.GPIO_Speed=GPIO_SPEED_FREQ_VERY_HIGH
PH14.Mode=RGB565
PH14.Signal=LTDC_G3
PH15.GPIOParameters=GPIO_Speed
PH15.GPIO_Speed=GPIO_SPEED_FREQ_VERY_HIGH
PH15.Mode=RGB565
PH15.Signal=LTDC_G4
PH2.GPIOParameters=GPIO_PuPd,GPIO_Label
PH2.GPIO_Label=RBTN_DOWN
PH2.GPIO_PuPd=GPIO_PULLUP
PH2.Signal=GPIO_Input
PH3.GPIOParameters=GPIO_PuPd,GPIO_Label
PH3.GPIO_Label=RBTN_RIGHT
PH3.GPIO_PuPd=GPIO_PULLUP
PH3.Signal=GPIO_Input
PH6.GPIOParameters=GPIO_Speed,GPIO_PuPd,GPIO_Label
PH6.GPIO_Label=TP_SCK
PH6.GPIO_PuPd=GPIO_PULLUP
PH6.GPIO_Speed=GPIO_SPEED_FREQ_HIGH
PH6.Signal=GPIO_Output
PH7.GPIOParameters=GPIO_Label
PH7.GPIO_Label=TP_PEN
PH7.Signal=GPIO_Input
PH9.GPIOParameters=GPIO_Speed
PH9.GPIO_Speed=GPIO_SPEED_FREQ_VERY_HIGH
PH9.Mode=RGB565
PH9.Signal=LTDC_R3
PI0.GPIOParameters=GPIO_Speed
PI0.GPIO_Speed=GPIO_SPEED_FREQ_VERY_HIGH
PI0.Mode=RGB565
PI0.Signal=LTDC_G5
PI1.GPIOParameters=GPIO_Speed
PI1.GPIO_Speed=GPIO_SPEED_FREQ_VERY_HIGH
PI1.Mode=RGB565
PI1.Signal=LTDC_G6
PI10.GPIOParameters=GPIO_Speed
PI10.GPIO_Speed=GPIO_SPEED_FREQ_VERY_HIGH
PI10.Mode=RGB565
PI10.Signal=LTDC_HSYNC
PI2.GPIOParameters=GPIO_Speed
PI2.GPIO_Speed=GPIO_SPEED_FREQ_VERY_HIGH
PI2.Mode=RGB565
PI2.Signal=LTDC_G7
PI3.GPIOParameters=GPIO_PuPd,GPIO_Label,GPIO_ModeDefaultOutputPP
PI3.GPIO_Label=TP_SDA
PI3.GPIO_ModeDefaultOutputPP=GPIO_MODE_OUTPUT_OD
PI3.GPIO_PuPd=GPIO_PULLUP
PI3.Signal=GPIO_Output
PI4.GPIOParameters=GPIO_Speed
PI4.GPIO_Speed=GPIO_SPEED_FREQ_VERY_HIGH
PI4.Mode=RGB565
PI4.Signal=LTDC_B4
PI5.GPIOParameters=GPIO_Speed
PI5.GPIO_Speed=GPIO_SPEED_FREQ_VERY_HIGH
PI5.Mode=RGB565
PI5.Signal=LTDC_B5
PI6.GPIOParameters=GPIO_Speed
PI6.GPIO_Speed=GPIO_SPEED_FREQ_VERY_HIGH
PI6.Mode=RGB565
PI6.Signal=LTDC_B6
PI7.GPIOParameters=GPIO_Speed
PI7.GPIO_Speed=GPIO_SPEED_FREQ_VERY_HIGH
PI7.Mode=RGB565
PI7.Signal=LTDC_B7
PI8.GPIOParameters=PinState,GPIO_PuPd,GPIO_Label
PI8.GPIO_Label=TP_CS
PI8.GPIO_PuPd=GPIO_PULLUP
PI8.PinState=GPIO_PIN_RESET
PI8.Signal=GPIO_Output
PI9.GPIOParameters=GPIO_Speed
PI9.GPIO_Speed=GPIO_SPEED_FREQ_VERY_HIGH
PI9.Mode=RGB565
PI9.Signal=LTDC_VSYNC
RCC.HSE_VALUE=25000000
RCC.SYSCLKFreq_VALUE=180000000
RCC.SYSCLKSource=RCC_SYSCLKSOURCE_PLLCLK
board=custom

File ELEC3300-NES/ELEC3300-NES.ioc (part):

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Mcu.Name=STM32F429I(E-G)Tx
Mcu.Package=LQFP176
Mcu.UserName=STM32F429IGTx
PA0/WKUP.GPIOParameters=GPIO_Label
PA0/WKUP.GPIO_Label=Btn_Up
PA0/WKUP.Signal=GPIO_Input
PA13.Mode=Serial_Wire
PA13.Signal=SYS_JTMS-SWDIO
PA14.Mode=Serial_Wire
PA14.Signal=SYS_JTCK-SWCLK
PA3.Signal=ADCx_IN3
PA4.Signal=ADCx_IN4
PA5.Signal=ADCx_IN5
PB0.Signal=ADCx_IN8
PB1.GPIOParameters=GPIO_Label
PB1.GPIO_Label=LED1
PB1.Signal=GPIO_Output
PB5.GPIOParameters=GPIO_Speed,GPIO_Label
PB5.GPIO_Label=LCD_BL
PB5.GPIO_Speed=GPIO_SPEED_FREQ_HIGH
PB5.Signal=GPIO_Output
PC0.Signal=FMC_SDNWE
PC10.Mode=SD_4_bits_Wide_bus
PC10.Signal=SDIO_D2
PC11.Mode=SD_4_bits_Wide_bus
PC11.Signal=SDIO_D3
PC12.Mode=SD_4_bits_Wide_bus
PC12.Signal=SDIO_CK
PC13.GPIOParameters=GPIO_PuPd,GPIO_Label
PC13.GPIO_Label=Btn_Left
PC13.GPIO_PuPd=GPIO_PULLUP
PC13.Signal=GPIO_Input
PC14/OSC32_IN.Mode=LSE-External-Oscillator
PC14/OSC32_IN.Signal=RCC_OSC32_IN
PC15/OSC32_OUT.Mode=LSE-External-Oscillator
PC15/OSC32_OUT.Signal=RCC_OSC32_OUT
PC2.Mode=SdramChipSelect1_1
PC2.Signal=FMC_SDNE0
PC3.Mode=SdramChipSelect1_1
PC3.Signal=FMC_SDCKE0
PC8.Mode=SD_4_bits_Wide_bus
PC8.Signal=SDIO_D0
PC9.Mode=SD_4_bits_Wide_bus
PC9.Signal=SDIO_D1
PD0.Signal=FMC_D2_DA2
PD1.Signal=FMC_D3_DA3
PD10.Signal=FMC_D15_DA15
PD14.Signal=FMC_D0_DA0
PD15.Signal=FMC_D1_DA1
PD2.Mode=SD_4_bits_Wide_bus
PD2.Signal=SDIO_CMD
PD8.Signal=FMC_D13_DA13
PD9.Signal=FMC_D14_DA14
PE0.Signal=FMC_NBL0
PE1.Signal=FMC_NBL1
PE10.Signal=FMC_D7_DA7
PE11.Signal=FMC_D8_DA8
PE12.Signal=FMC_D9_DA9
PE13.Signal=FMC_D10_DA10
PE14.Signal=FMC_D11_DA11
PE15.Signal=FMC_D12_DA12
PE2.GPIOParameters=GPIO_Label
PE2.GPIO_Label=SD_Card_Check
PE2.Signal=GPIO_Input
PE4.GPIOParameters=GPIO_Label
PE4.GPIO_Label=Joy_R_Btn
PE4.Signal=GPIO_Input
PE6.GPIOParameters=GPIO_Label
PE6.GPIO_Label=Joy_L_Btn
PE6.Signal=GPIO_Input
PE7.Signal=FMC_D4_DA4
PE8.Signal=FMC_D5_DA5
PE9.Signal=FMC_D6_DA6
PF0.Signal=FMC_A0
PF1.Signal=FMC_A1
PF10.GPIOParameters=GPIO_Speed
PF10.GPIO_Speed=GPIO_SPEED_FREQ_VERY_HIGH
PF10.Mode=RGB565
PF10.Signal=LTDC_DE
PF11.Signal=FMC_SDNRAS
PF12.Signal=FMC_A6
PF13.Signal=FMC_A7
PF14.Signal=FMC_A8
PF15.Signal=FMC_A9
PF2.Signal=FMC_A2
PF3.Signal=FMC_A3
PF4.Signal=FMC_A4
PF5.Signal=FMC_A5
PG0.Signal=FMC_A10
PG1.Signal=FMC_A11
PG11.GPIOParameters=GPIO_Speed
PG11.GPIO_Speed=GPIO_SPEED_FREQ_VERY_HIGH
PG11.Mode=RGB565
PG11.Signal=LTDC_B3
PG15.Signal=FMC_SDNCAS
PG2.Signal=FMC_A12
PG4.Signal=FMC_A14_BA0
PG5.Signal=FMC_A15_BA1
PG6.GPIOParameters=GPIO_Speed
PG6.GPIO_Speed=GPIO_SPEED_FREQ_VERY_HIGH
PG6.Mode=RGB565
PG6.Signal=LTDC_R7
PG7.GPIOParameters=GPIO_Speed
PG7.GPIO_Speed=GPIO_SPEED_FREQ_VERY_HIGH
PG7.Mode=RGB565
PG7.Signal=LTDC_CLK
PG8.Signal=FMC_SDCLK
PH0/OSC_IN.Mode=HSE-External-Oscillator
PH0/OSC_IN.Signal=RCC_OSC_IN
PH1/OSC_OUT.Mode=HSE-External-Oscillator
PH1/OSC_OUT.Signal=RCC_OSC_OUT
PH10.GPIOParameters=GPIO_Speed
PH10.GPIO_Speed=GPIO_SPEED_FREQ_VERY_HIGH
PH10.Mode=RGB565
PH10.Signal=LTDC_R4
PH11.GPIOParameters=GPIO_Speed
PH11.GPIO_Speed=GPIO_SPEED_FREQ_VERY_HIGH
PH11.Mode=RGB565
PH11.Signal=LTDC_R5
PH12.GPIOParameters=GPIO_Speed
PH12.GPIO_Speed=GPIO_SPEED_FREQ_VERY_HIGH
PH12.Mode=RGB565
PH12.Signal=LTDC_R6
PH13.GPIOParameters=GPIO_Speed
PH13.GPIO_Speed=GPIO_SPEED_FREQ_VERY_HIGH
PH13.Mode=RGB565
PH13.Signal=LTDC_G2
PH14.GPIOParameters=GPIO_Speed
PH14.GPIO_Speed=GPIO_SPEED_FREQ_VERY_HIGH
PH14.Mode=RGB565
PH14.Signal=LTDC_G3
PH15.GPIOParameters=GPIO_Speed
PH15.GPIO_Speed=GPIO_SPEED_FREQ_VERY_HIGH
PH15.Mode=RGB565
PH15.Signal=LTDC_G4
PH2.GPIOParameters=GPIO_PuPd,GPIO_Label
PH2.GPIO_Label=Btn_Down
PH2.GPIO_PuPd=GPIO_PULLUP
PH2.Signal=GPIO_Input
PH3.GPIOParameters=GPIO_PuPd,GPIO_Label
PH3.GPIO_Label=Btn_Right
PH3.GPIO_PuPd=GPIO_PULLUP
PH3.Signal=GPIO_Input
PH6.GPIOParameters=GPIO_Speed,GPIO_PuPd,GPIO_Label
PH6.GPIO_Label=TP_SCK
PH6.GPIO_PuPd=GPIO_PULLUP
PH6.GPIO_Speed=GPIO_SPEED_FREQ_HIGH
PH6.Signal=GPIO_Output
PH7.GPIOParameters=GPIO_Label
PH7.GPIO_Label=TP_PEN
PH7.Signal=GPIO_Input
PH9.GPIOParameters=GPIO_Speed
PH9.GPIO_Speed=GPIO_SPEED_FREQ_VERY_HIGH
PH9.Mode=RGB565
PH9.Signal=LTDC_R3
PI0.GPIOParameters=GPIO_Speed
PI0.GPIO_Speed=GPIO_SPEED_FREQ_VERY_HIGH
PI0.Mode=RGB565
PI0.Signal=LTDC_G5
PI1.GPIOParameters=GPIO_Speed
PI1.GPIO_Speed=GPIO_SPEED_FREQ_VERY_HIGH
PI1.Mode=RGB565
PI1.Signal=LTDC_G6
PI10.GPIOParameters=GPIO_Speed
PI10.GPIO_Speed=GPIO_SPEED_FREQ_VERY_HIGH
PI10.Mode=RGB565
PI10.Signal=LTDC_HSYNC
PI2.GPIOParameters=GPIO_Speed
PI2.GPIO_Speed=GPIO_SPEED_FREQ_VERY_HIGH
PI2.Mode=RGB565
PI2.Signal=LTDC_G7
PI3.GPIOParameters=GPIO_PuPd,GPIO_Label,GPIO_ModeDefaultOutputPP
PI3.GPIO_Label=TP_SDA
PI3.GPIO_ModeDefaultOutputPP=GPIO_MODE_OUTPUT_OD
PI3.GPIO_PuPd=GPIO_PULLUP
PI3.Signal=GPIO_Output
PI4.GPIOParameters=GPIO_Speed
PI4.GPIO_Speed=GPIO_SPEED_FREQ_VERY_HIGH
PI4.Mode=RGB565
PI4.Signal=LTDC_B4
PI5.GPIOParameters=GPIO_Speed
PI5.GPIO_Speed=GPIO_SPEED_FREQ_VERY_HIGH
PI5.Mode=RGB565
PI5.Signal=LTDC_B5
PI6.GPIOParameters=GPIO_Speed
PI6.GPIO_Speed=GPIO_SPEED_FREQ_VERY_HIGH
PI6.Mode=RGB565
PI6.Signal=LTDC_B6
PI7.GPIOParameters=GPIO_Speed
PI7.GPIO_Speed=GPIO_SPEED_FREQ_VERY_HIGH
PI7.Mode=RGB565
PI7.Signal=LTDC_B7
PI8.GPIOParameters=PinState,GPIO_PuPd,GPIO_Label
PI8.GPIO_Label=TP_CS
PI8.GPIO_PuPd=GPIO_PULLUP
PI8.PinState=GPIO_PIN_RESET
PI8.Signal=GPIO_Output
PI9.GPIOParameters=GPIO_Speed
PI9.GPIO_Speed=GPIO_SPEED_FREQ_VERY_HIGH
PI9.Mode=RGB565
PI9.Signal=LTDC_VSYNC
RCC.HSE_VALUE=25000000
RCC.SYSCLKFreq_VALUE=120000000
RCC.SYSCLKSource=RCC_SYSCLKSOURCE_PLLCLK
board=custom

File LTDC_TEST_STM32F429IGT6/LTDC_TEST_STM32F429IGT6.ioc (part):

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Mcu.Name=STM32F429I(E-G)Tx
Mcu.Package=LQFP176
Mcu.UserName=STM32F429IGTx
PA0/WKUP.Signal=ADCx_IN0
PA1.Signal=ADCx_IN1
PA10.Mode=Asynchronous
PA10.Signal=USART1_RX
PA13.Mode=Serial_Wire
PA13.Signal=SYS_JTMS-SWDIO
PA14.Mode=Serial_Wire
PA14.Signal=SYS_JTCK-SWCLK
PA2.Mode=Asynchronous
PA2.Signal=USART2_TX
PA3.Mode=Asynchronous
PA3.Signal=USART2_RX
PA4.GPIOParameters=GPIO_Label
PA4.GPIO_Label=IMU-NSS
PA4.Mode=NSS_Signal_Hard_Output
PA4.Signal=SPI1_NSS
PA5.GPIOParameters=GPIO_Label
PA5.GPIO_Label=IMU-SCK
PA5.Mode=Full_Duplex_Master
PA5.Signal=SPI1_SCK
PA7.GPIOParameters=GPIO_Label
PA7.GPIO_Label=IMU-MOSI
PA7.Mode=Full_Duplex_Master
PA7.Signal=SPI1_MOSI
PA9.Mode=Asynchronous
PA9.Signal=USART1_TX
PB12.Mode=Full_Duplex_Master
PB12.Signal=I2S2_WS
PB13.Mode=Full_Duplex_Master
PB13.Signal=I2S2_CK
PB4.GPIOParameters=GPIO_Label
PB4.GPIO_Label=IMU-MISO
PB4.Mode=Full_Duplex_Master
PB4.Signal=SPI1_MISO
PB6.GPIOParameters=GPIO_Label
PB6.GPIO_Label=Touch_Screen_SCL
PB6.Mode=I2C
PB6.Signal=I2C1_SCL
PB7.GPIOParameters=GPIO_Label
PB7.GPIO_Label=Touch_Screen_SDA
PB7.Mode=I2C
PB7.Signal=I2C1_SDA
PC10.Mode=SD_4_bits_Wide_bus
PC10.Signal=SDIO_D2
PC11.Mode=SD_4_bits_Wide_bus
PC11.Signal=SDIO_D3
PC12.Mode=SD_4_bits_Wide_bus
PC12.Signal=SDIO_CK
PC14/OSC32_IN.Mode=LSE-External-Oscillator
PC14/OSC32_IN.Signal=RCC_OSC32_IN
PC15/OSC32_OUT.Mode=LSE-External-Oscillator
PC15/OSC32_OUT.Signal=RCC_OSC32_OUT
PC2.Mode=Full_Duplex_Master
PC2.Signal=I2S2_ext_SD
PC3.Mode=Full_Duplex_Master
PC3.Signal=I2S2_SD
PC4.GPIOParameters=GPIO_Label
PC4.GPIO_Label=IMU-INT
PC4.Signal=GPIO_Output
PC8.Mode=SD_4_bits_Wide_bus
PC8.Signal=SDIO_D0
PC9.Mode=SD_4_bits_Wide_bus
PC9.Signal=SDIO_D1
PD0.Mode=CAN_Activate
PD0.Signal=CAN1_RX
PD2.Mode=SD_4_bits_Wide_bus
PD2.Signal=SDIO_CMD
PD8.Mode=Asynchronous
PD8.Signal=USART3_TX
PD9.Mode=Asynchronous
PD9.Signal=USART3_RX
PF0.Mode=I2C
PF0.Signal=I2C2_SDA
PF1.Mode=I2C
PF1.Signal=I2C2_SCL
PF4.GPIOParameters=GPIO_Label
PF4.GPIO_Label=NRF-IRQ-IT
PF4.Signal=GPXTI4
PF5.GPIOParameters=GPIO_Label
PF5.GPIO_Label=NRF-CE
PF5.Signal=GPIO_Output
PF6.GPIOParameters=GPIO_Label
PF6.GPIO_Label=NRF-NSS
PF6.Mode=NSS_Signal_Hard_Output
PF6.Signal=SPI5_NSS
PF7.GPIOParameters=GPIO_Label
PF7.GPIO_Label=NRF-SCK
PF7.Mode=Full_Duplex_Master
PF7.Signal=SPI5_SCK
PF8.GPIOParameters=GPIO_Label
PF8.GPIO_Label=NRF-MISO
PF8.Mode=Full_Duplex_Master
PF8.Signal=SPI5_MISO
PF9.GPIOParameters=GPIO_Label
PF9.GPIO_Label=NRF-MOSI
PF9.Mode=Full_Duplex_Master
PF9.Signal=SPI5_MOSI
PH0/OSC_IN.Mode=HSE-External-Oscillator
PH0/OSC_IN.Signal=RCC_OSC_IN
PH1/OSC_OUT.Mode=HSE-External-Oscillator
PH1/OSC_OUT.Signal=RCC_OSC_OUT
PH13.Mode=CAN_Activate
PH13.Signal=CAN1_TX
RCC.HSE_VALUE=8000000
RCC.SYSCLKFreq_VALUE=180000000
RCC.SYSCLKSource=RCC_SYSCLKSOURCE_PLLCLK
board=custom

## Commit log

2023-09-30 add gitignore before init project
2023-09-30 update gitignore
2023-09-30 Setup .ioc
    STM32F429RGT6 Basic Setup
2023-09-30 adding RTOS
2023-09-30 add discussionWS
2023-10-05 Add discussion worksheet
2023-10-05 add doc cache ignore
2023-10-11 add lvgl submodule
2023-10-11 Revert "add lvgl submodule"
    This reverts commit a9932f689c38373ef1fa65db0fb73adc1e56ff12.
2023-10-11 switch to stable version v.8.3
2023-10-12 upload project
2023-10-12 push simply led blinky code
2023-10-12 NOW IT WORKS!!!!!!!!
2023-10-12 add RTC
2023-10-12 led blinky code done
2023-10-15 update launch file
2023-10-15 it said it can't find the start up file, but startup is there...
2023-10-15 now can build through cmake
2023-10-15 Open own project
2023-10-15 added some files
2023-10-16 LCD light on
2023-10-21 Hartin Create project try to copy libraries
2023-10-30 Fix build
2023-10-30 now can build
2023-10-31 add gitignore and seems cmake can build
2023-10-31 add rtos
2023-10-31 add remaining files
2023-10-31 clang format
2023-10-31 led blinky but in rtos
    it's not ideal but hey it works what can you do
2023-10-31 Add os.h
2023-11-01 refactor the rtos structure to more robocon style :+1
2023-11-01 start configure development board's io from its gpio
2023-11-01 init another led on extension board
2023-11-01 trying to sync the config of from 正點原子 but fail
2023-11-01 now can show full screen color but can't show text
2023-11-01 rename lcd_ltdc.c to lcd.c
2023-11-01 too much debug
2023-11-01 Try to solve DMA2D problem
2023-11-02 start from zero
2023-11-02 enable SDRAM (haven't test)
2023-11-02 Deleted file in .metadata from git
2023-11-02 Finish 2 layers LTDC drive TFT-LCD Screen
2023-11-02 Add DMA2D support for faster framebuffer operations & draw point works!!!!
2023-11-02 minor restructure
2023-11-02 draw line
2023-11-02 remove chinese comments
2023-11-02 tft_prints
2023-11-02 Add tft_update()
    Only works for chars/strings
2023-11-05 Attempting to config lvgl
    want to move the conf files to our own user dir but cmake does not want to cooperate
2023-11-05 Forgot to stage conf files lmao
2023-11-05 Fix submodule
2023-11-05 add lvgl module and finish its config
2023-11-05 remove lvgl
2023-11-05 Add lvgl v8.3 as submodule
2023-11-05 try ft5206 module driver, but not working
2023-11-06 move code and test migration
2023-11-06 it now can build but RAM overflow
2023-11-07 RAM overflow 2MB (I cry)
2023-11-07 finish fake boot animation
2023-11-07 Enable touchscreen
2023-11-07 finish set up ADC for joystick & merge with touch screen
2023-11-07 update ioc for Joystick ADC and Button gpio
2023-11-07 add SWIO, DMA & FATFS config generated by .ioc
2023-11-08 update the adc setting and unfinished cmakelist
2023-11-08 lvgl touch screen works now
2023-11-08 no build error now
2023-11-08 update cmake list for lvgl
2023-11-08 move the dir of the files
2023-11-08 add RTOS from .ioc and change sys timebase to TIM1
2023-11-08 Edge triggering (kind of)
    why does this work
2023-11-08 RTOS works but FATFS not that work
2023-11-08 Fix touch
2023-11-08 fix fatfs testing function
2023-11-08 Move boot animation files over (but breaks)
    It can't work properly when we display other stuff I'll debug later
2023-11-08 Add tic tac toe
    looks bad but idc
2023-11-09 Add button and joystick support to controller
2023-11-09 Display with image
2023-11-09 Fix SDIO hardware flow control and add LVGL tick hook
2023-11-09 Updated GPIO and LVGL configurations
2023-11-09 Add button control
2023-11-09 add es8388 from .ioc
2023-11-09 Fix boot animation
2023-11-09 Clean up code (or maybe not)
2023-11-10 Added I2C and ES8388 audio support
2023-11-15 yoink code
2023-11-17 pcb done
2023-11-22 Init board
2023-11-22 Init UART (it doesn't work feelsbadman)
    also moved threads to freertos.c
    got tired of threads being wiped every time I gened code
2023-11-23 Fix clock
2023-11-23 Updated PDF for scheme
2023-11-24 Attempting SPI for IMU (doesn't work fml)
2023-11-26 Init GPIO buttons
2023-11-26 Enable UART
2023-11-26 Enable controller thread
2023-11-26 Allow lvgl to parse button inputs
2023-11-26 add Schem
2023-11-26 change GPIO of the joystick
2023-11-26 Fix misc errors
2023-11-26 Get reading(?) from IMU
    idk what I'm reading but the numbers change so
2023-11-26 Move NES stuff over
    tbh idk why we have so many directories this is getting annoying
2023-11-26 Remove lvgl in an attempt to make NES fit
    doesn't help fml
    maybe time to look at the other repos I have no clue
    or maybe compiler optimizations?
    time to kms
2023-11-27 Add ADC and DMA interrupt handlers
2023-11-27 fix joystick button adc
2023-11-27 add pcb schem
2023-11-27 Revert "Remove lvgl in an attempt to make NES fit"
    This reverts commit 687e00b089a0f6059b18d3f9251ed831faed4ed6.
2023-11-27 Forcibly reduce size
    fox can only play super mario
2023-11-27 finish joystick reading
2023-11-27 Blue screen of death
    this is fine
2023-11-27 idk anymore
2023-11-27 Change loadframe
    doesn't help
2023-11-28 doesn't work
2023-11-28 cam use button for detection
2023-11-28 tune right joystick offset and scale and enable imu power save mode
2023-11-28 add touch power save as well
2023-11-28 update the fatfs
2023-11-28 now can detect SD card insert state
2023-11-28 Project builds
2023-11-28 Fix movement
2023-11-28 Can kind of play ig
    idk
2023-11-28 Still broken
    istg idk why I'm still wasting time on this smh my head
2023-11-29 Can build
2023-11-29 fix compile bug
2023-11-29 add halfly done pong (still have screen display problem)
2023-11-29 slightly better display
2023-11-29 now multi-player works
2023-11-29 Add randomization to ball starting position and kind of finish everything
2023-11-29 Update GPIO configuration and add TIM3 initialization
2023-11-29 Can rotate
    1fps yay
2023-11-29 only commited half idk why
2023-11-29 Update TFT driver and ADC sampling time
2023-11-29 Now can use lvgl Main page
2023-11-29 Finish basic Main page UI
2023-11-29 Add event callback for TFT pages
2023-11-29 Upgrade tetris
    kind of
2023-11-29 Remove high score
2023-11-29 still doesn't work I give up
2023-11-29 Hacky fix for tetris endgame screen
2023-11-29 Fix power saving mode and add text display for non-LVGL display
2023-11-30 Home page can swap to tetris page
    pain
2023-11-30 clock tf
2023-11-30 Pong thread size too large don't ask
2023-11-30 thread size balancing
    cool
2023-11-30 Brightness toggle
2023-11-30 Misc fixes
2023-11-30 Use os_create_thread
2023-11-30 Fix buffer issue
    my code sucks
2023-12-11 change directory
